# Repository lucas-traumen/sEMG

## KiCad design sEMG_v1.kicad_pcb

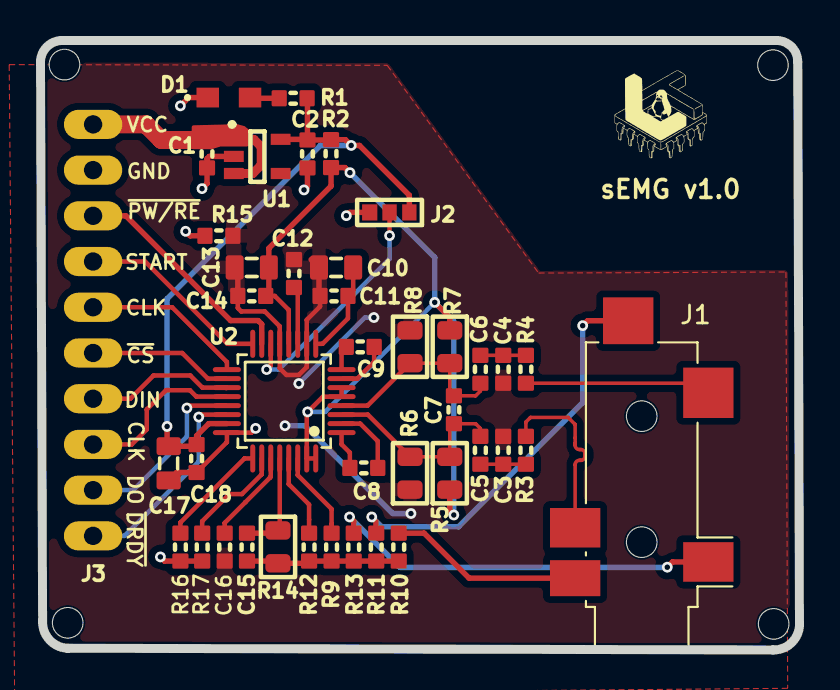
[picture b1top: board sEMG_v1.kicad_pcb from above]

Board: 2 copper layers, 42.2 x 33.9 mm, 41 parts (0 on the bottom side), 37 nets.

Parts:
C1, C2, C12, C16: 1uF; C_0603
C3, C4, C15: 47pF; C_0603
C5, C6: 2.2nF; C_0603
C7: 1nF; C_0603
C8, C9: 4.7nF; C_0603
C10, C13, C18: 10uF; C_0805
C11, C14, C17: 0.1uF; C_0603
D1: Led; LED_APT2012EC
J1: Conn_01x10; SJ2-3593D-SMT-TR
J2: Jump3_0603_Open
J3: pad-1x10
R1: 330R; R_0603
R2, R9, R10, R11, R15: 0R; R_0603
R3, R4: 22K; R_0603
R5, R6, R7, R8, R14: 1M; R0805
R12: 100k; R_0603
R13: 100K; R_0603
R16, R17: 10K; R_0603
U1: SOT_RG1_DIO-L
U2: TI ADS1292RIPBSR

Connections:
/AVDD: C13.2, C14.2, R2.1, R5.1, R7.1, U2.5 (IN2N), U2.6 (IN2P), U2.12 (AVDD), U2.31 (RESP_MODP/IN3P), U2.32 (RESP_MODN/IN3N)
/AVSS: C3.2, C4.2, C10.1, C11.1, C12.2, C13.1, C14.1, C16.2, R6.1, R8.1, R15.2, U2.10 (VREFN), U2.13 (AVSS)
/CLK: J3.5, U2.17 (CLK)
/DIN: J3.7, U2.19 (DIN)
/DN: J1.R, R3.1
/DOUT: J3.9, U2.21 (DOUT)
/DP: J1.T, R4.1
/RN: J1.RN, R10.2
/S: J1.S, R13.2
/SCLK: J3.8, U2.20 (SCLK)
/START: J3.4, U2.16 (START)
/TN: J1.TN, R11.2
/VCC3V3: C2.1, C17.2, C18.2, J2.1 (A), R1.1, R2.2, U1.5 (VOUT), U2.23 (DVDD)
/VCC5V: C1.1, J3.1, U1.1 (VIN), U1.3 (EN)
/~CS: J3.6, U2.18 (CS#)
/~DRDY: J3.10, U2.22 (DRDY#)
/~PWDN/RESET: J3.3, U2.15 (PWDN#/RESET#)
GND: C1.2, C2.2, C17.1, C18.1, D1.1 (K), J2.3 (B), J3.2, R15.1, R16.2, R17.2, U1.2 (GND), U2.24 (DGND)
unnamed: C3.1, C5.2, R3.2
unnamed: C4.1, C6.2, R4.2
unnamed: C15.2, R9.2, R10.1, R11.1, R12.2, R13.1, R14.2
unnamed: D1.2 (A), R1.2
unnamed: J2.2 (C), U2.14 (CLKSEL)
unnamed: R17.1, U2.26 (GPIO1/RCLK1)
unnamed: R16.1, U2.25 (GPIO2/RCLK2)
unnamed: C5.1, C7.1, R5.2, R6.2, U2.3 (IN1N)
unnamed: C6.1, C7.2, R7.2, R8.2, U2.4 (IN1P)
unnamed: C8.2, U2.1 (PGA1N)
unnamed: C8.1, U2.2 (PGA1P)
unnamed: C9.2, U2.7 (PGA2N)
unnamed: C9.1, U2.8 (PGA2P)
unnamed: C15.1, R14.1, U2.28 (RLDINV)
unnamed: R12.1, U2.29 (RLDIN/RLDREF)
unnamed: R9.1, U2.30 (RLDOUT)
unnamed: C12.1, U2.11 (VCAP1)
unnamed: C16.1, U2.27 (VCAP2)
unnamed: C10.2, C11.2, U2.9 (VREFP)

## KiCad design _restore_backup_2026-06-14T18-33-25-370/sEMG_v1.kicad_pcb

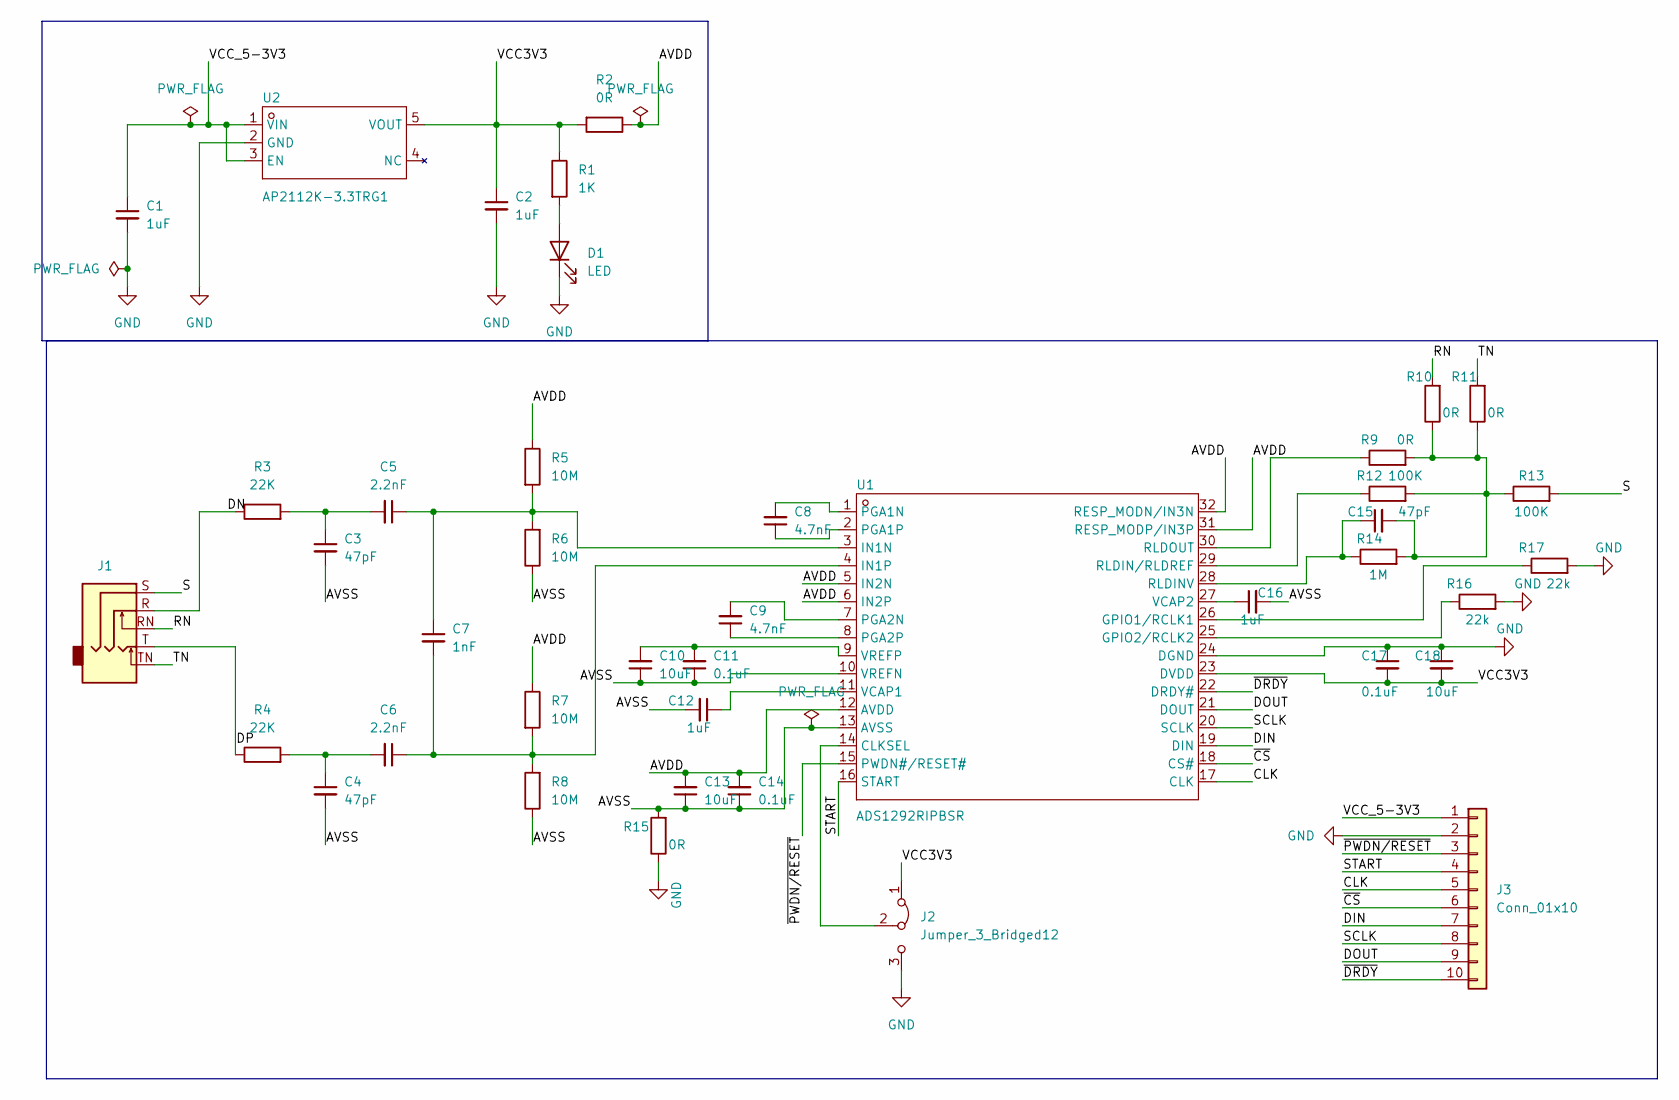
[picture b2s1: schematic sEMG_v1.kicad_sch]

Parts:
C1, C2, C12, C16: 1uF; CC0603KRX7R7BB105
C3, C4, C15: 47pF; CC0603JRNPO9BN470
C5, C6: 2.2nF; CC0603JRNPO9BN152
C7: 1nF; CC0603JRNPO9BN102
C8, C9: 4.7nF; CC0603JRNPO9BN472
C10, C13, C18: 10uF; CC0805KKX7R7BB106
C11, C14, C17: 0.1uF; CC0603KRX7R7BB104
D1: LED; LED_APT2012EC
J1: AudioJack3_SwitchTR; Jack_3.5mm_CUI_SJ2-3593D-SMT_Horizontal
J2: Jumper_3_Bridged12; SolderJumper-3_P1.3mm_Open_Pad1.0x1.5mm_NumberLabels
J3: Conn_01x10; c
R1: 1K; RC0603FR-071KL
R2, R9, R10, R11, R15: 0R; RC0603JR-070RL
R3, R4: 22K; TNPW060322K0BEEA
R5, R6, R7, R8: 10M; RC0805FR-0710ML
R12, R13: 100K; TNPW0603100KBEEA
R14: 1M; TNPW08051M00BEEA
R16, R17: 22k; RC0603JR-070RL
U1: TQFP-32_L5.0-W5.0-P0.50-LS7.0-TL; Manufacturer Part ADS1292RIPBSR; LCSC Part Name 低功耗、2通道、24位生物电位测量模拟前端
U2: SOT-25-5_L2.9-W1.6-P0.95-LS2.8-BL; Manufacturer Part AP2112K-3.3TRG1; LCSC Part Name 输入6V 输出3.3V 600mA

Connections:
/AVDD: C13.2, C14.2, R2.1, R5.1, R7.1, U1.5 (IN2N), U1.6 (IN2P), U1.12 (AVDD), U1.31 (RESP_MODP/IN3P), U1.32 (RESP_MODN/IN3N)
/AVSS: C3.2, C4.2, C10.1, C11.1, C12.2, C13.1, C14.1, C16.2, R6.1, R8.1, R15.2, U1.10 (VREFN), U1.13 (AVSS)
/CLK: J3.5, U1.17 (CLK)
/DIN: J3.7, U1.19 (DIN)
/DN: J1.R, R3.1
/DOUT: J3.9, U1.21 (DOUT)
/DP: J1.T, R4.1
/RN: J1.RN, R10.2
/S: J1.S, R13.2
/SCLK: J3.8, U1.20 (SCLK)
/START: J3.4, U1.16 (START)
/TN: J1.TN, R11.2
/VCC3V3: C2.1, C17.2, C18.2, J2.1 (A), R1.1, R2.2, U1.23 (DVDD), U2.5 (VOUT)
/VCC_5-3V3: C1.1, J3.1, U2.1 (VIN), U2.3 (EN)
/~CS: J3.6, U1.18 (CS#)
/~DRDY: J3.10, U1.22 (DRDY#)
/~PWDN/RESET: J3.3, U1.15 (PWDN#/RESET#)
GND: C1.2, C2.2, C17.1, C18.1, D1.1 (K), J2.3 (B), J3.2, R15.1, R16.2, R17.2, U1.24 (DGND), U2.2 (GND)
unnamed: C3.1, C5.2, R3.2
unnamed: C4.1, C6.2, R4.2
unnamed: C15.2, R9.2, R10.1, R11.1, R12.2, R13.1, R14.2
unnamed: D1.2 (A), R1.2
unnamed: J2.2 (C), U1.14 (CLKSEL)
unnamed: R17.1, U1.26 (GPIO1/RCLK1)
unnamed: R16.1, U1.25 (GPIO2/RCLK2)
unnamed: C5.1, C7.1, R5.2, R6.2, U1.3 (IN1N)
unnamed: C6.1, C7.2, R7.2, R8.2, U1.4 (IN1P)
unnamed: C8.2, U1.1 (PGA1N)
unnamed: C8.1, U1.2 (PGA1P)
unnamed: C9.2, U1.7 (PGA2N)
unnamed: C9.1, U1.8 (PGA2P)
unnamed: C15.1, R14.1, U1.28 (RLDINV)
unnamed: R12.1, U1.29 (RLDIN/RLDREF)
unnamed: R9.1, U1.30 (RLDOUT)
unnamed: C12.1, U1.11 (VCAP1)
unnamed: C16.1, U1.27 (VCAP2)
unnamed: C10.2, C11.2, U1.9 (VREFP)

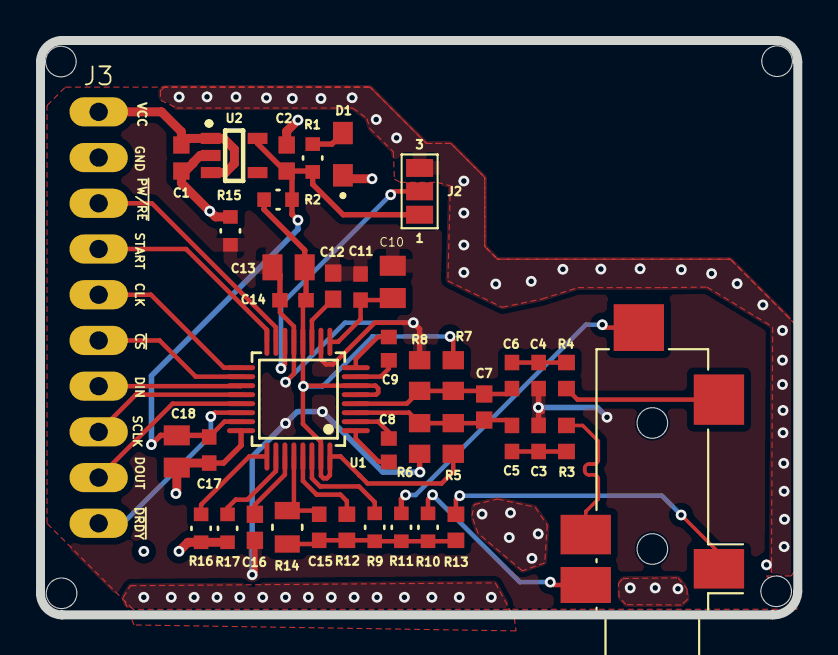
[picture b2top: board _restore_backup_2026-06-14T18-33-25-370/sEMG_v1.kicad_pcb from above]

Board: 2 copper layers, 42.1 x 31.9 mm, 41 parts (0 on the bottom side), 37 nets.

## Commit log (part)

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2026-04-22 sEMG v1
2026-05-13 update v1
2026-06-19 completed sEMG v1.0
2026-06-19 modified footprint sEMG v1.0
